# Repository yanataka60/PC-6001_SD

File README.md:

# PC-6001にSD-CARDからロード、セーブ機能

　PC-6001でSD-CARDからロード、セーブ機能を実現するものです。

　対応機種は初代PC-6001です。

　PC-6001mk2以降の機種でも動作しますが、MODE1、MODE2のみの動作となります。また、PC-6601、PC-6601SRはドライブ数切替スイッチは0として使ってください。なお、PC-6001mk2以降の機種では裏RAMにBASIC-ROMをコピーしてパッチを当てますのでBASIC-ROMを差し替える必要はありません。

　対応しているCMT形式は、P6形式(拡張子はP6、CASのどちらでも大丈夫)とP6T形式です。

　CMTからの読み込み実行に数分掛かっていたゲームも数十秒で実行できます。

　なお、Arduino、ROMへ書き込むための機器が別途必要となります。

.JPG)

.JPG)

## 対応できないもの
　BASIC-ROMのCMT関連ルーチンにパッチを当てたROMに差し替えることでSD-CARDへのアクセスを実現していますのでBASIC-ROMのCMT関連ルーチンをコールせず独自にCMTからLOADするソフト（ロードランナー等）は対応できないので途中で止まります。

## 回路図
### PC-6001_SD基板
　KiCadフォルダ/PC-6001_SD内のPC-6001_SD.pdfを参照してください。

[回路図](https://github.com/yanataka60/PC-6001_SD/blob/main/Kicad/PC-6001_SD/PC-6001_SD.pdf)

### BASIC-ROM挿し替え用基板
　KiCadフォルダ/ROM_SOCKET内のROM_SOCKET.pdfを参照してください。

[回路図](https://github.com/yanataka60/PC-6001_SD/blob/main/Kicad/ROM_SOCKET/ROM_SOCKET.pdf)

## 部品
### PC-6001_SD基板
|番号|品名|数量|備考|
| ------------ | ------------ | ------------ | ------------ |
||J2、J3のいずれか(注1)|||
|J2|Micro_SD_Card_Kit|1|秋月電子通商 AE-microSD-LLCNV (注2)|
|J3|MicroSD Card Adapter|1|Arduino等に使われる5V電源に対応したもの (注4)|
|U1|74LS04|1||
|U2|74LS30|1||
|U3|74LS32|1||
|U4|8255|1||
|U5|2764/28C64相当品|1||
|U6|SRAM 62256相当品|1||
|U7|Arduino_Pro_Mini_5V|1|Atmega328版を使用 168版は不可。(注3)|
|C1 C2 C3 C4 C5 C6|積層セラミックコンデンサ 0.1uF|6||
|C7|電解コンデンサ 16v100uF|1||
||ピンヘッダ|2Pin分|Arduino_Pro_MiniにはA4、A5用のピンヘッダが付いていないため別途調達が必要です 秋月電子通商 PH-1x40SGなど|
||ピンソケット(任意)|26Pin分|Arduino_Pro_Miniを取り外し可能としたい場合に調達します 秋月電子通商 FHU-1x42SGなど|

　　　注1)J2又はJ3のどちらかを選択して取り付けてください。

　　　注2)秋月電子通商　AE-microSD-LLCNVのJ1ジャンパはショートしてください。

　　　注3)Arduino Pro MiniはA4、A5ピンも使っています。

　　　注4)MicroSD Card Adapterを使う場合

　　　　　J3に取り付けます。

　　　　　MicroSD Card Adapterについているピンヘッダを除去してハンダ付けするのが一番確実ですが、J3の穴にMicroSD Card Adapterをぴったりと押しつけ、裏から多めにハンダを流し込むことでハンダ付けをする方法もあります。なお、この方法の時にはしっかりハンダ付けが出来たかテスターで導通を確認しておいた方が安心です。

ハンダ付けに自信のない方はJ2の秋月電子通商　AE-microSD-LLCNVをお使いください。AE-microSD-LLCNVならパワーLED、アクセスLEDが付いています。

### BASIC-ROM挿し替え用基板
|番号|品名|数量|備考|
| ------------ | ------------ | ------------ | ------------ |
|S1|ジャンパー||27128はHigh(5V)、27256はLow(GND)に固定|
|S2|ピンヘッダＬ型 1x3(3P)|1|秋月電子通商 PH-1X3RG(2)など|
||ピンソケット(メス) 1x3(3P)又はコネクタ用ハウジング 3P + ケーブル用コネクタ|1|秋月電子通商 FH-1x3SG/RH 2226A-03 2226TGなど|
||3Pトグルスイッチ 1回路2接点 パネル取付用|1|秋月電子通商 1MS1-T1-B1-M1-Q-Nなど|
||配線材|約30cmx3||
|U1|27128又は27256相当品|1|28C256は不可、29C256は可|
|U2|基板用リードフレーム又は細ピンヘッダ|12Pinx2|秋月電子通商 SS2.54-6SN、PHA-1x40SGなど|

## ROMへの書込み
　Z80フォルダ内のEXT_ROM.binをROMライター(TL866II Plus等)を使って2764又は28C64に書き込みます。

## Arduinoプログラム
　PC-6001mk2_SDと全く同じものを使用しています。

　Arduino IDEを使ってPC-6001mk2_SDプロジェクトArduinoフォルダのPC-6001mk2_SDフォルダ内PC-6001mk2_SD.inoを書き込みます。

　SdFatライブラリを使用しているのでArduino IDEメニューのライブラリの管理からライブラリマネージャを立ち上げて「SdFat」をインストールしてください。

　「SdFat」で検索すれば見つかります。「SdFat」と「SdFat - Adafruit Fork」が見つかりますが「SdFat」のほうを使っています。

注)Arduinoを基板に直付けしている場合、Arduinoプログラムを書き込むときは、カートリッジスロットから抜き、74LS04を外したうえで書き込んでください。

## BASIC-ROMの挿し替え
### BASIC-ROMの抽出
　まず、PC-6001_SD基板を完成させ、拡張スロットに挿入して電源を入れます。

　画面に「PC-6001_SD Launcher」と表示されるので、STOPキー又は「1」コマンド、「B」コマンドでBASICを起動します。

　入力待ちになったら「EXEC &H4013[CR]」と入力するとBASIC-ROMの内容をSD-CARDに保存するプログラムが実行されます。

.JPG)

.JPG)

.JPG)

.JPG)

　終わったらSD-CARDを抜き、Windowsパソコン等で内容を確認すると「ROM60A.CAS」と「ROM60B.CAS」という二つのファイルが作成されているはずです。

　「ROM60A.CAS」「ROM60B.CAS」とも拡張子を「.bin」に変更します。

　「ROM60A.bin」はBASIC-ROM全体(0000h～3FFFh)のダンプファイルです。Emulator等に使ってください。

　「ROM60B.bin」はBASIC-ROM前半(0000h～1FFFh)のダンプファイルでこちらにパッチを当て挿し替えることになります。

### BASIC-ROMへのパッチあて
　まず、「ROM60B.bin」をコピーし「ROM60C.bin」を作ります。

　「ROM60C.bin」の以下のアドレスを修正します。

|ADDRESS|修正前|修正後|
| ------------ | ------------ | ------------ |
|1A61|C5 D5 E5|C3 04 40|
|1A70|C5 D5 E5|C3 07 40|
|1AB8|C5 D5 E5|C3 0A 40|
|1ACC|C5 D5 E5|C3 0D 40|
|1B06|C5 D5 E5|C3 10 40|

　「ROM60B.bin」と「ROM60C.bin」をマージし、「ROM60.bin」として保存します。ROM60B.binが0000h～1FFFh、ROM60C.binが2000h～3FFFhとなります。

　出来上がった「ROM60.bin」を27128又は27256等に焼きます。

### BASIC-ROM挿し替え用基板の装着

　BASIC-ROM挿し替え用基板に27128を使うときはA14(S1)はHigh(5V)に固定します。

　27256を使うときは、A14(S1)はLow(GND)にします。が、A14もA13と同様に3Pスイッチで切り替えられるようにすれば4000h～7FFFhまでを使って4つまでBASIC-ROMを切り替えられるようにも出来ます。

.JPG)

.JPG)

.JPG)

　3PトグルスイッチによりCMTとSDを切り替えられるようにします。

　3PトグルスイッチはRS-232C用のパネルに穴を開けて取り付けるのがいいと思います。

.JPG)

.JPG)

.JPG)

## 接続
　カートリッジスロットに挿入します。

.JPG)

　カートリッジスロットへの抜き差しに基板のみでは不便です。

　STLフォルダに基板を載せられるトレイの3Dデータを置いたので出力して使うと便利です。

　PC-6601、PC-6601SRはドライブ数切替スイッチは0として使ってください。

## SD-CARD
　出来れば8GB以下のSDカードを用意してください。

　ArduinoのSdFatライブラリは、SD規格(最大2GB)、SDHC規格(2GB～32GB)に対応していますが、SDXC規格(32GB～2TB)には対応していません。

　また、SDHC規格のSDカードであっても32GB、16GBは相性により動作しないものがあるようです。

　FAT16又はFAT32が認識できます。NTFSは認識できません。

　ルートに置かれた拡張子が「.P6T」又は「.CAS」の形式ファイルのみ認識できます。(以外のファイル、フォルダも表示されますがLOAD実行の対象になりません)

　ファイル名は拡張子を除いて32文字まで、ただし半角カタカナ、及び一部の記号はArduinoが認識しないので使えません。パソコンでファイル名を付けるときはアルファベット、数字および空白でファイル名をつけてください。

　起動直後の画面は横32文字表示です。拡張子を含めて27文字以下にしたほうが画面が乱れません。

## MODE選択
### 初代PC-6001
　MODE1、MODE2の切り替えは、PC-6001_SD基板上のRAM切替スイッチにより選択します。16K側でMODE1、32K側でMODE2です。

### PC-6001mk2以降
　PC-6001_SD基板上のRAM切替スイッチは16K側にしてください。

　通常に電源ON、またはRESETしたときにはMODE1となります。

　MODE2にしたい時は、数字の2キーを押したまま、電源ON、またはRESETしてください。

## 使い方
起動直後は拡張ROMのプログラムが走り、以下のコマンドが使えます。

### Launcherコマンド
#### 1[CR]
次に「How Many Pages?(1-4)」と聞いてくるので画面数を入力すると入力された数字の画面数でSD対応にして起動します。

#### B[CR]
SD対応せずにBASICを起動します。

[STOP]キーと動作は同じです。

#### [STOP]キー
SD対応せずにBASICを起動します。

B[CR]と動作は同じです。

#### F[CR]又はF 文字列[CR]
文字列を入力せずにF[CR]のみ入力するとSD-CARDルートディレクトリにあるファイルの一覧を表示します。

文字列を付けて入力すればSD-CARDルートディレクトリにあるその文字列から始まるファイルの一覧を表示します。

10件表示したところで指示待ちになるので打ち切るならESC又は↑を入力すると打ち切られ、Bキーで前の10件に戻ります。それ以外のキーで次の10件を表示します。

　行頭に「*L 」を付加して表示してあるので実行したいファイルにカーソルキーを合わせて[CR]キーを押すだけでLOAD可能です。

　LOADの挙動については次のLコマンドの記述を参照してください。

　表示される順番は、登録順となりファイル名アルファベッド順などのソートした順で表示することはできません。

##### 例)
　　F[CR]

　　F S[CR]

　　F SP[CR]

#### L DOSファイル名[CR]
指定したDOSフィル名のファイルをSD-CARDからLOADします。

ファイル名の最後の「.P6T」「.CAS」は有っても無くても構いませんが、無い場合は「.P6T」が指定されたものとみなします。

　例)

　　L TEST.P6T -> DOSファイル名「TEST.P6T」を読み込みます。

　　L TEST.CAS -> DOSファイル名「TEST.CAS」を読み込みます。

　　L TEST -> DOSファイル名「TEST.P6T」を読み込みます。

　選択したファイルが「P6T」形式の場合、設定されたPagesで起動したうえで自動実行文字列を実行します。

　選択したファイルが「CAS」形式の場合、「How Many Pages?(1-4)」と聞いてくるので画面数を入力、次に「Auto Run?(y/c/n)」と聞いてくるので「y」とすれば最後に「Auto Run?(y/c/n)」と聞いてくるので「y」とすれば起動直後にCLOAD[CR]RUN[CR]が実行され、「c」とすればCLOAD[CR]だけが実行、「n」とすれば何も実行されません。

#### 操作上の注意
　~~「SD-CARD INITIALIZE ERROR」と表示されたときは、SD-CARDをいったん抜き再挿入したうえでArduinoをリセットしてください。~~

　~~SD-CARDにアクセスしていない時に電源が入ったままで SD-CARDを抜いた後、再挿入しSD-CARDにアクセスすると「SD-CARD INITIALIZE ERROR」となる場合があります。再挿入した場合にはSD-CARDにアクセスする前にArduinoを必ずリセットしてください。~~

　~~SD-CARDの抜き差しは電源を切った状態で行うほうがより確実です。~~

　(2024.3.12) SD-CARDにアクセスしていない時に電源が入ったままでSD-CARDを抜くと再度SD-CARDを挿入してもSD-CARDにアクセスできない問題を解消しました。(Arduinoを最新版に書き換えてください)

　再度SD-CARDを挿入した後、Fコマンド、Lコマンド、CLOAD、CSAVE等でSD-CARDに3回ほどアクセスすれば復旧します。

### BASICコマンド
#### CLOAD "DOSファイル名"[CR]
指定したDOSフィル名のBASICプログラムをSD-CARDからLOADします。

ファイル名は6文字以内で必須です。6文字以上入力された場合には7文字以降は無視されます。ファイル名を入力せずにCLOAD[CR]とすると暴走します。

ファイル名の前に"(ダブルコーテーション)は必須ですが、ファイル名の後ろに"(ダブルコーテーション)は有っても無くても構いません。

ファイル名の最後に「.CAS」は必要ありません。「.CAS」が指定されたものとみなします。

　例)

　　CLOAD "TEST" -> DOSファイル名「TEST.CAS」を読み込みます。

　　CLOAD "TESTTEST" -> DOSファイル名「TESTTE.CAS」を読み込みます。

　　CLOAD "TEST.BAS.CMT" -> DOSファイル名「TEST.BA.CMT」を読み込みます。

#### CSAVE "DOSファイル名"[CR]
BASICプログラムを指定したDOSフィル名でSD-CARDに上書きSAVEします。

ファイル名は6文字以内で必須です。6文字以上入力された場合には7文字以降は無視されます。

ファイル名の前に"(ダブルコーテーション)は必須ですが、ファイル名の後ろに"(ダブルコーテーション)は有っても無くても構いません。

ファイル名の最後の「.CAS」は必要ありません。「.CAS」が指定されたものとみなします。

　例)

　　CSAVE "TEST" -> 「TEST.CAS」で保存される。

　　CSAVE "TESTTEST" -> 「TESTTE.CAS」で保存される。

## RAMのテスト
　RAMCHECKフォルダ内のramcheck.p6tをSDカードにコピーして実行してください。

　8400h～F6FFhまでのRAMをCHECKできます。

　なお、終了時に「?SN Error in 50」と表示されますが、BASICプログラムを上書きしてRAMCHECKを行っているためで異常ではありません。

## 謝辞
　基板の作成に当たり以下のデータを使わせていただきました。ありがとうございました。

　Arduino Pro Mini

　　https://github.com/g200kg/kicad-lib-arduino

　AE-microSD-LLCNV

　　https://github.com/kuninet/PC-8001-SD-8kRAM

## 追記
　2023. 3. 4 AUTO STARTの選択肢をy/c/nとし、CLOADも実行しない選択を追加

　　　　　　CLOAD、CSAVEがLOAD、SAVEと誤表記されていたものを修正

　2024.1.15 SDカードは8GB以下が望ましいことを追記。

　2024.3.12 電源が入ったままでSD-CARDを抜くと再度SD-CARDを挿入してもSD-CARDにアクセスできない問題を解消した。

　2025.3.20 P6形式が使えることが伝わりにくい表記を修正した。

　2025.9.11 RAMCHECKプログラムを追加。

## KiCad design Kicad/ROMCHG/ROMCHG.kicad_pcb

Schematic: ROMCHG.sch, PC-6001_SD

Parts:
S1, S2: SLIDE_SWITCH_3P; PinHeader_1x03_P2.54mm_Vertical
U1: 27256; DIP-28_W15.24mm_LongPads
U2: 2364; DIP-24_W15.24mm_LongPads

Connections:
+5V: S1.3, S2.3, U1.1, U1.28, U2.24
GND: S1.1, S2.1, U1.14, U1.22, U2.12
unnamed: S1.2, U1.27
unnamed: S2.2, U1.26
unnamed: U1.2, U2.21
unnamed: U1.3, U2.1
unnamed: U1.4, U2.2
unnamed: U1.5, U2.3
unnamed: U1.6, U2.4
unnamed: U1.7, U2.5
unnamed: U1.8, U2.6
unnamed: U1.9, U2.7
unnamed: U1.10, U2.8
unnamed: U1.11, U2.9
unnamed: U1.12, U2.10
unnamed: U1.13, U2.11
unnamed: U1.15, U2.13
unnamed: U1.16, U2.14
unnamed: U1.17, U2.15
unnamed: U1.18, U2.16
unnamed: U1.19, U2.17
unnamed: U1.20, U2.20
unnamed: U1.21, U2.19
unnamed: U1.23, U2.18
unnamed: U1.24, U2.22
unnamed: U1.25, U2.23

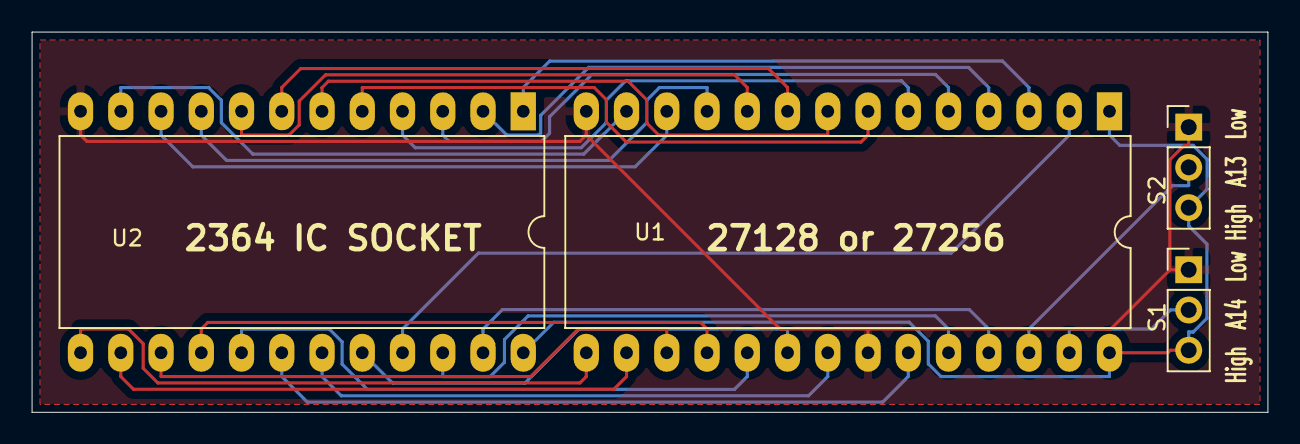
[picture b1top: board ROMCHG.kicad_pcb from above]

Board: 2 copper layers, 78.0 x 24.0 mm, 4 parts (0 on the bottom side), 26 nets.

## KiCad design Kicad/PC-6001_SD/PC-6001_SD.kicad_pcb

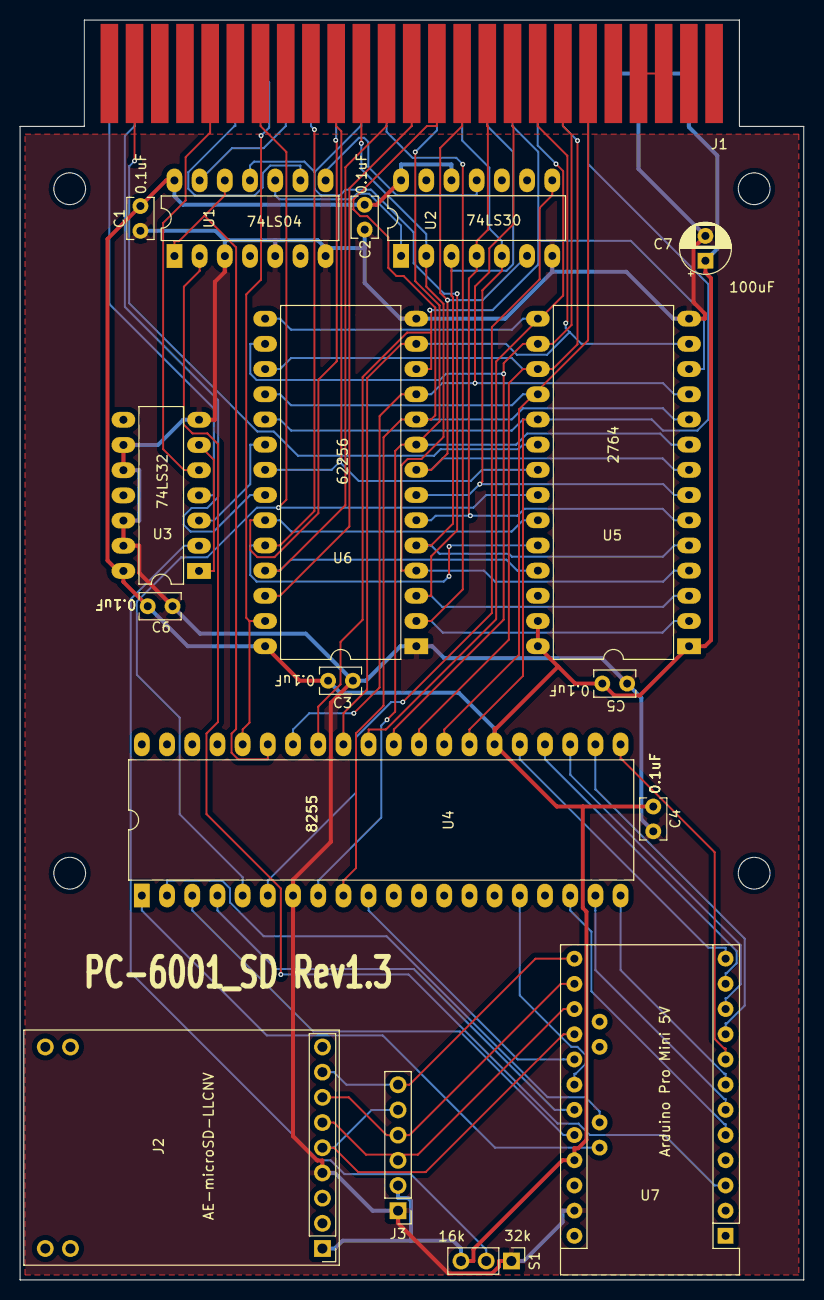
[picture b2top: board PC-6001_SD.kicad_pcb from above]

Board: 2 copper layers, 79.0 x 127.0 mm, 22 parts (0 on the bottom side), 59 nets.

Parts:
C1, C2, C3, C4, C5, C6: 0.1uF; C_Rect_L4.0mm_W2.5mm_P2.50mm
C7: 100uF; CP_Radial_D5.0mm_P2.50mm
J1: PC-8001 BUS; BUS_50Pin
J2: Micro_SD_Card_Kit; AE-microSD-LLCNV
J3: MicroSD Card Adapter; PinHeader_1x06_P2.54mm_Vertical
MH1, MH2, MH3, MH4: MountingHole_3.2mm_M3
S1: 32k 16k; PinHeader_1x03_P2.54mm_Vertical
U1: 74LS04; DIP-14_W7.62mm_LongPads
U2: 74LS30; DIP-14_W7.62mm_LongPads
U3: 74LS32; DIP-14_W7.62mm_LongPads
U4: 8255; DIP-40_W15.24mm_LongPads
U5: 2764; DIP-28_W15.24mm_LongPads
U6: HM62256BLP; DIP-28_W15.24mm_LongPads
U7: Arduino_Pro_Mini_5V; Arduino_Pro_Mini

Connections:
+5V: C1.2, C2.2, C3.1, C4.1, C5.1, C6.2, C7.1, J1.45, J1.47, J2.1, J3.2, S1.3, U1.14, U2.12, U2.14, U3.14, U4.26, U5.1, U5.27, U5.28, U6.28, U7.21
/A0: J1.28, U4.9, U5.10, U6.10
/A1: J1.27, U4.8, U5.9, U6.9
/A2: J1.30, U2.6, U5.8, U6.8
/A3: J1.29, U2.5, U5.7, U6.7
/A4: J1.32, U2.4, U5.6, U6.6
/A5: J1.31, U2.3, U5.5, U6.5
/A6: J1.22, U2.2, U5.4, U6.4
/A7: J1.21, U1.11, U5.3, U6.3
/A8: J1.24, U5.25, U6.25
/A9: J1.17, U5.24, U6.24
/A10: J1.20, U5.21, U6.21
/A11: J1.19, U5.23, U6.23
/A12: J1.23, U5.2, U6.2
/A13: J1.26, U6.26
/CS: J2.8, J3.6, U7.13
/D0: J1.34, U4.34, U5.11, U6.11
/D1: J1.33, U4.33, U5.12, U6.12
/D2: J1.36, U4.32, U5.13, U6.13
/D3: J1.35, U4.31, U5.15, U6.15
/D4: J1.38, U4.30, U5.16, U6.16
/D5: J1.37, U4.29, U5.17, U6.17
/D6: J1.40, U4.28, U5.18, U6.18
/D7: J1.39, U4.27, U5.19, U6.19
/MISO: J2.6, J3.3, U7.15
/MOSI: J2.7, J3.4, U7.14
/MSW1: J1.44, J1.46
/SCK: J2.5, J3.5, U7.16
/~CS2: J1.4, U5.20
/~DRD2: J1.3, U6.22
/~EXCAS: J1.10, U3.5
/~IORQ: J1.11, U1.9
/~RAS2: J1.1, U3.4
/~RD: J1.14, U4.5, U5.22
/~RESET: J1.15, U1.13
/~WR: J1.13, U4.36, U6.27
GND: C1.1, C2.1, C3.2, C4.2, C5.2, C6.1, C7.2, J1.41, J1.43, J2.4, J3.1, S1.1, U1.3, U1.5, U1.7, U2.7, U3.7, U3.9, U3.10, U3.12, U3.13, U4.7, U5.14, U6.1, U6.14, U7.23
unnamed: S1.2, U3.2
unnamed: U1.1, U1.12, U4.35
unnamed: U1.2, U7.3
unnamed: U1.8, U2.11
unnamed: U1.10, U2.1
unnamed: U2.8, U4.6
unnamed: U3.1, U3.6
unnamed: U3.3, U6.20
unnamed: U4.1, U7.A5
unnamed: U4.2, U7.A4
unnamed: U4.3, U7.20
unnamed: U4.4, U7.19
unnamed: U4.10, U7.17
unnamed: U4.16, U7.18
unnamed: U4.18, U7.5
unnamed: U4.19, U7.6
unnamed: U4.20, U7.7
unnamed: U4.21, U7.8
unnamed: U4.22, U7.9
unnamed: U4.23, U7.10
unnamed: U4.24, U7.11
unnamed: U4.25, U7.12
